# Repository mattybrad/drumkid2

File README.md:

# Drumkid 2
Aleatoric drum machine, uses random numbers to generate/alter drumbeats. This project is the successor to the original Drumkid, which was released in 2020. Drumkid 2 runs on a Raspberry Pi Pico. This repo contains both code for the Pico and PCB files.

## Setup
I used the official Raspberry Pi Pico installer for Windows to set up the Pico toolchain for Visual Studio Code. Remember to update the repo's submodules. The SD card code submodule is a specific commit (v1.1.2), not the latest version. Have included the .vscode folder, which may be different on non-Windows systems?

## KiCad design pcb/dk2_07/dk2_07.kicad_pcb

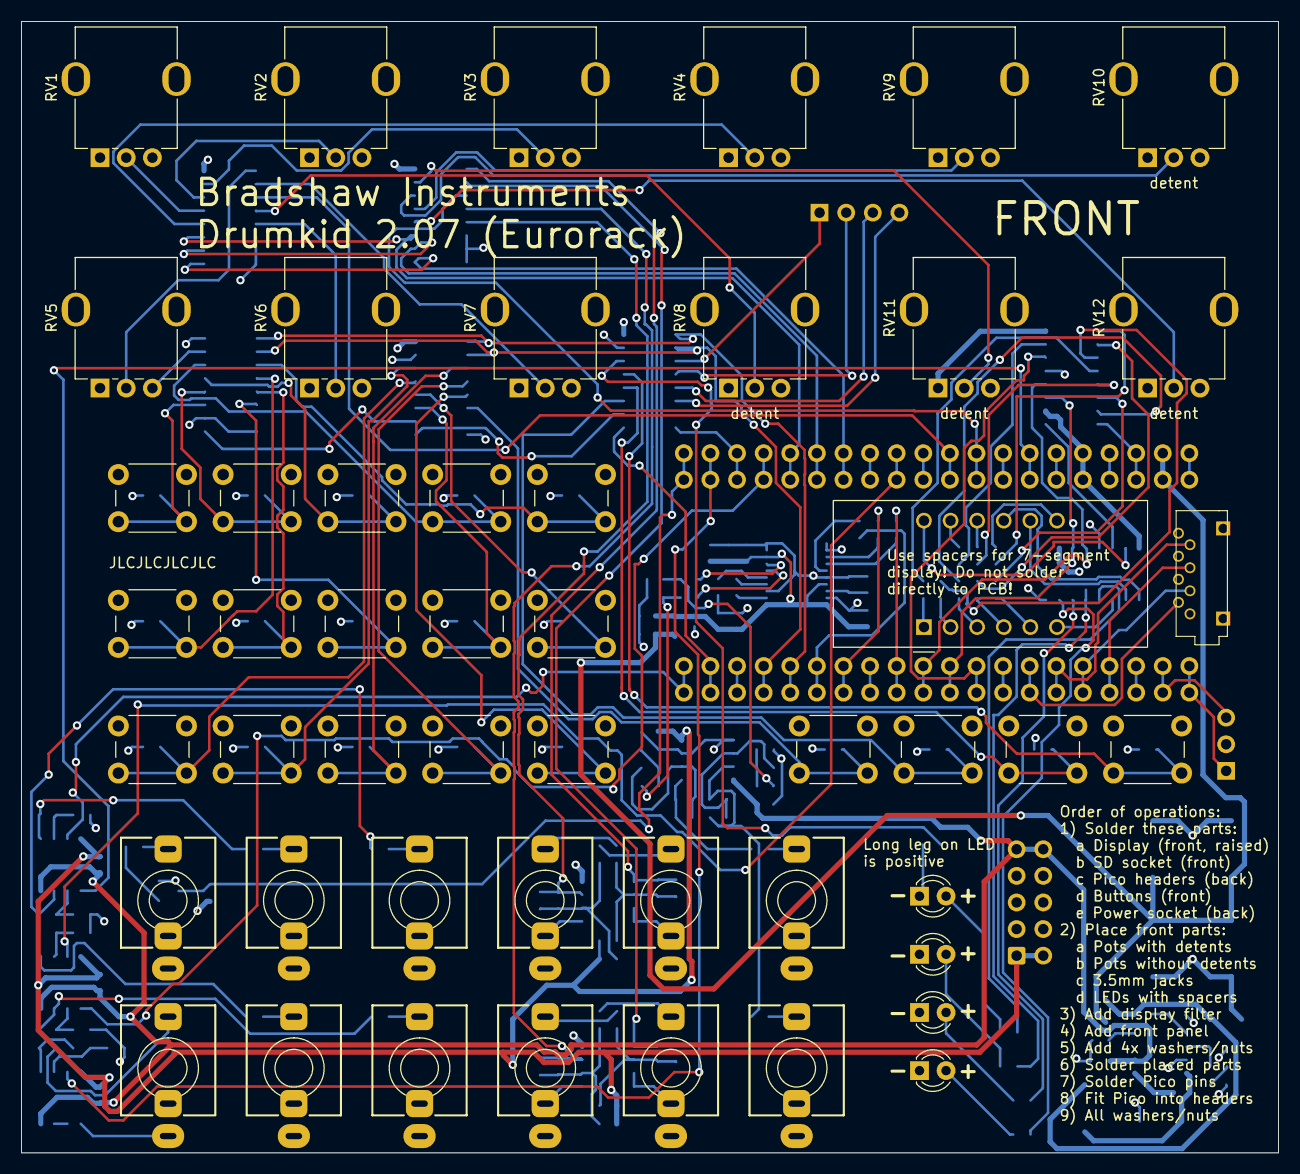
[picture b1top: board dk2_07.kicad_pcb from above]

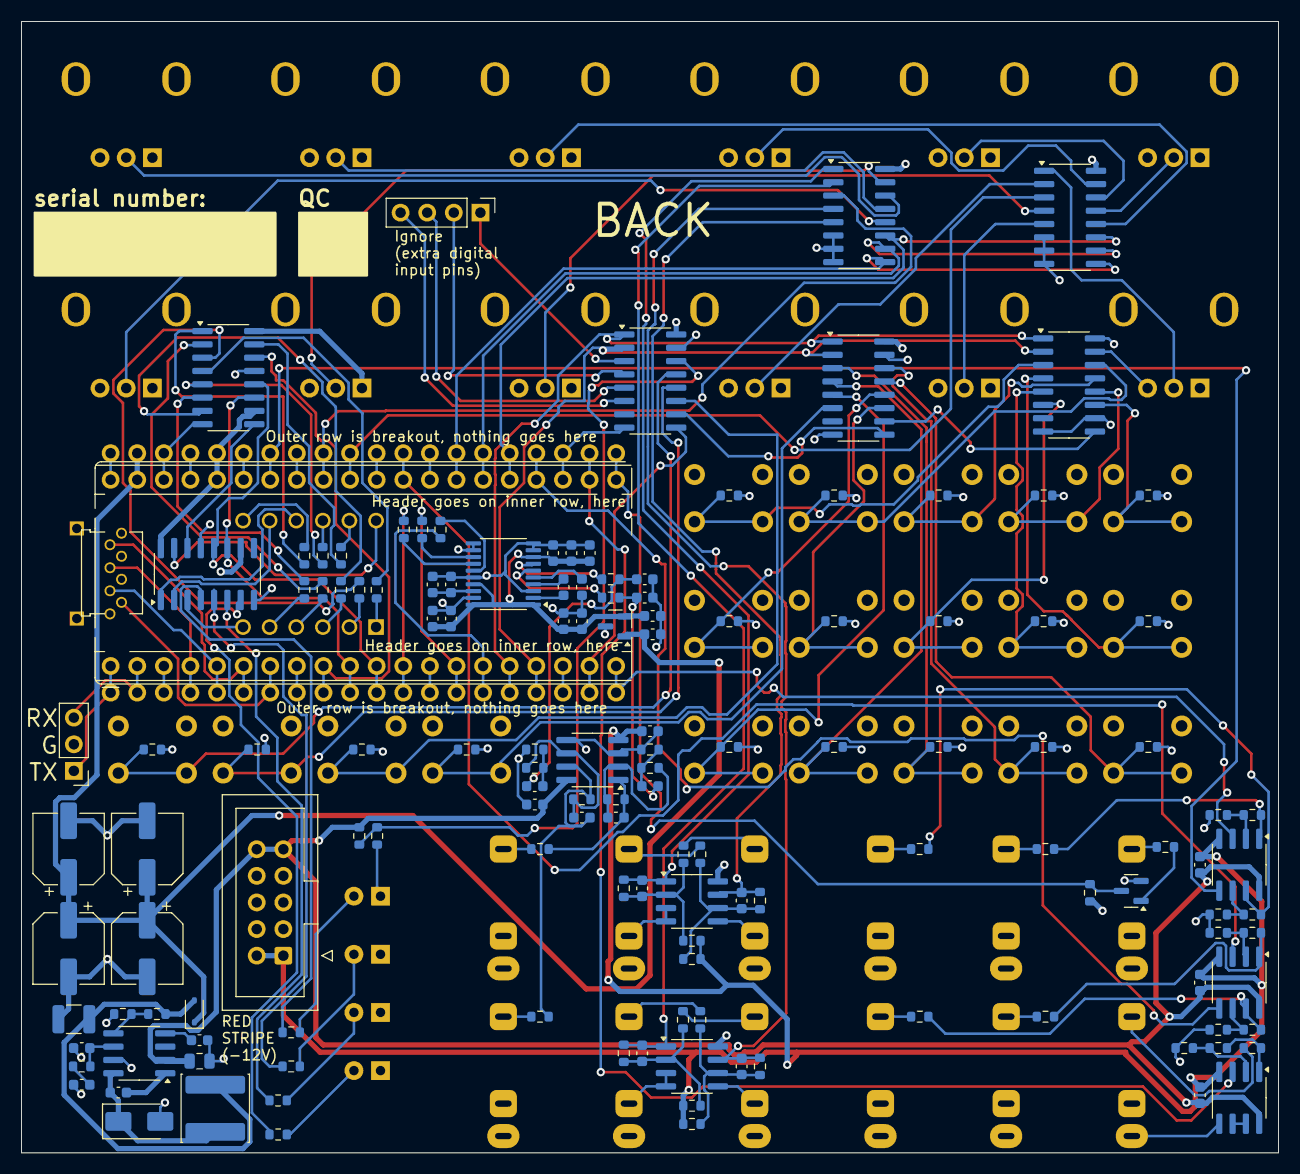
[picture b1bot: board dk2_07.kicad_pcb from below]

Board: 4 copper layers, 120.0 x 108.0 mm, 189 parts (140 on the bottom side), 155 nets.

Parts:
A1: RaspberryPi_Pico; RaspberryPi_Pico_Common_THT_dk2
C1, C2, C3, C4: 1n; C_0603_1608Metric
C5, C9, C24, C29: 1uF; C_0603_1608Metric
C6: 22uF; C_0805_2012Metric
C7: 100nF; C_0603_1608Metric
C8: 8.2nF; C_0603_1608Metric
C10: 1nF; C_0603_1608Metric
C11: 10pF; C_0603_1608Metric
C12: 47uF; C_1210_3225Metric
C13, C14, C15, C16: 470uF; CP_Elec_6.3x7.7
C17, C18, C25, C30, C34: 10uF; C_0603_1608Metric
C19, C20, C36, C37, C38: 100n; C_0603_1608Metric
C21, C22: 18p; C_0603_1608Metric
C23, C28, C31, C32: 0.1uF; C_0603_1608Metric
C26, C27: 2.2uF; C_0603_1608Metric
C33, C35: 2.2nF; C_0603_1608Metric
D1, D2, D3, D4: LED; LED_D3.0mm
D5: B340A; D_SMA
D6: 1N5819WS; D_SOD-323
J1: Trigger_Out_1; Jack_3.5mm_QingPu_WQP-PJ398SM_Vertical
J2: Trigger_Out_2; Jack_3.5mm_QingPu_WQP-PJ398SM_Vertical
J3: Sync_In; Jack_3.5mm_QingPu_WQP-PJ398SM_Vertical
J4: Euro_Out_1; Jack_3.5mm_QingPu_WQP-PJ398SM_Vertical
J5: Micro_SD_Card; YAMAICHI_MICROSD_VERTICAL
J6: Trigger_Out_3; Jack_3.5mm_QingPu_WQP-PJ398SM_Vertical
J7: Trigger_Out_4; Jack_3.5mm_QingPu_WQP-PJ398SM_Vertical
J8: Sync_Out; Jack_3.5mm_QingPu_WQP-PJ398SM_Vertical
J9: Euro_Out_2; Jack_3.5mm_QingPu_WQP-PJ398SM_Vertical
J10: Conn_01x03_Pin; PinHeader_1x03_P2.54mm_Vertical
J11: CV_In_1; Jack_3.5mm_QingPu_WQP-PJ398SM_Vertical
J12: CV_In_2; Jack_3.5mm_QingPu_WQP-PJ398SM_Vertical
J13: CV_In_3; Jack_3.5mm_QingPu_WQP-PJ398SM_Vertical
J14: CV_In_4; Jack_3.5mm_QingPu_WQP-PJ398SM_Vertical
J15: Conn_01x04_Pin; PinHeader_1x04_P2.54mm_Vertical
J16: Eurorack_Power; IDC-Header_2x05_P2.54mm_Vertical
L1: 10uH; L_Sunlord_SWPA6045S
Q1: MMBT3904; SOT-23
R1, R2, R3, R4, R5, R6, R7, R8, R9, R10, R11, R12: 75R; R_0603_1608Metric
R13, R14, R15, R16, R17, R18, R19, R20, R21, R22, R23, R24, R25, R26, R27, R28, R43, R44, R45, R47: 10k; R_0603_1608Metric
R29, R31, R35, R37: 240k; R_0603_1608Metric
R30, R32, R36, R38, R42, R64, R65, R66, R67, R70, R71, R72, R73, R76, R77: 100k; R_0603_1608Metric
R33, R34, R39, R40: 33k; R_0603_1608Metric
R41: 330k; R_0603_1608Metric
R46: 43.2k; R_0603_1608Metric
R48: 1.65k; R_0603_1608Metric
R49, R50, R53, R54: 39k; R_0603_1608Metric
R51, R52: 5.6k; R_0603_1608Metric
R55, R56, R68, R69, R74, R75, R78: 1k; R_0603_1608Metric
R57, R58, R59: 56R; R_0603_1608Metric
R60, R61: 470R; R_0603_1608Metric
R62: 100K; R_0603_1608Metric
R63: 10K; R_0603_1608Metric
RV1, RV2, RV3, RV4, RV5, RV6, RV7, RV8, RV9, RV10, RV11, RV12: 10k; Potentiometer_Alps_RK09K_vertical_biggerholes
SW1, SW2, SW3, SW4, SW5, SW6, SW7, SW8, SW9, SW10, SW11, SW12, SW13, SW14, SW15, SW16, SW17, SW18, SW19: SW_Push; SW_PUSH_6mm
U1, U2: 74HC595; SOIC-16_3.9x9.9mm_P1.27mm
U3: CA56-12EWA; SR410361N
U4, U5, U10: 74HC165; SOIC-16_3.9x9.9mm_P1.27mm
U6, U9: 74HC4051; SOIC-16_3.9x9.9mm_P1.27mm
U7, U8: MCP6002-xSN; SOIC-8_3.9x4.9mm_P1.27mm
U11: AP7333-33SAG; SOT-23
U12: TPS54331DR; SOIC-8_3.9x4.9mm_P1.27mm
U13, U15, U16, U17: TL072; SOIC-8_3.9x4.9mm_P1.27mm
U14: PCM5102; TSSOP-20_4.4x6.5mm_P0.65mm

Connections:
12V DETECTION: R41.1, R42.2, U10.14 (D3)
165_CLOCK: A1.17 (GPIO13), U4.2 (CP), U5.2 (CP), U10.2 (CP)
165_DATA: A1.19 (GPIO14), U10.9 (Q7)
165_LOAD: A1.16 (GPIO12), U4.1 (~PL), U5.1 (~PL), U10.1 (~PL)
595_CLOCK: A1.10 (GPIO7), U1.11 (SRCLK), U2.11 (SRCLK)
595_DATA: A1.9 (GPIO6), U1.14 (SER)
595_LATCH: A1.11 (GPIO8), U1.12 (RCLK), U2.12 (RCLK)
4051_ADDRESS_A: A1.25 (GPIO19), U6.11 (S0), U9.11 (S0)
4051_ADDRESS_B: A1.26 (GPIO20), U6.10 (S1), U9.10 (S1)
4051_ADDRESS_C: A1.27 (GPIO21), U6.9 (S2), U9.9 (S2)
4051_READING_0: A1.31 (GPIO26_ADC0), U6.3 (A)
4051_READING_1: A1.32 (GPIO27_ADC1), U9.3 (A)
+3.3V: A1.36 (3V3), J5.4 (VDD), R63.1, RV1.1, RV2.1, RV3.1, RV4.1, RV5.1, RV6.1, RV7.1, RV8.1, RV9.1, RV10.1, RV11.1, RV12.1, SW1.1, SW2.1, SW3.1, SW4.1, SW5.1, SW6.1, SW7.1, SW8.1, SW9.1, SW10.1, SW11.1, SW12.1, SW13.1, SW14.1, SW15.1, SW16.1, SW17.1, SW18.1, SW19.1, U1.10 (~SRCLR), U1.16 (VCC), U2.10 (~SRCLR), U2.16 (VCC), U4.16 (VCC), U5.16 (VCC), U6.16 (VCC), U7.8 (V+), U8.8 (V+), U9.16 (VCC), U10.16 (VCC)
+3.3VDAC: C9.1, C23.1, C24.1, C25.1, C28.1, C30.1, C32.1, C34.1, U11.2 (VO), U14.1 (CPVDD), U14.8 (AVDD), U14.17 (XSMT), U14.20 (DVDD)
+5V: A1.39 (VSYS), C5.1, C13.1, C14.1, C15.1, C16.1, D6.1 (K), U11.1 (VI)
+12V: C6.1, C19.1, C36.1, C37.1, C38.1, J16.9, J16.10, R41.2, U12.2 (VIN), U13.8 (V+), U15.8 (V+), U16.8 (V+), U17.8 (V+)
-12V: C20.2, C36.2, C37.2, C38.2, J16.1, J16.2, R29.1, R31.1, R35.1, R37.1, U13.4 (V-), U15.4 (V-), U16.4 (V-), U17.4 (V-)
/Shift register in 1/DATA_OUT: U4.9 (Q7), U5.10 (DS)
/Shift register in 2/DATA_OUT: U5.9 (Q7), U10.10 (DS)
CV_IN_1: C1.2, R33.2, U7.1, U9.1 (A4)
CV_IN_2: C2.2, R34.2, U7.7, U9.5 (A5)
CV_IN_3: C3.2, R39.2, U8.1, U9.2 (A6)
CV_IN_4: C4.2, R40.2, U8.7, U9.4 (A7)
DAC_BCLK: A1.14 (GPIO10), R57.1
DAC_DOUT: A1.12 (GPIO9), R58.1
DAC_LRC: A1.15 (GPIO11), R59.1
EURO_OUT_1: J4.T, R55.2
EURO_OUT_2: J9.T, R56.2
GND: A1.3 (GND), A1.8 (GND), A1.13 (GND), A1.18 (GND), A1.23 (GND), A1.28 (GND), A1.33 (AGND), A1.38 (GND), C5.2, C6.2, C8.2, C9.2, C10.2, C11.2, C12.2, C13.2, C14.2, C15.2, C16.2, C19.2, C20.1, C23.2, C24.2, C25.2, C27.2, C28.2, C29.2, C30.2, C31.2, C32.2, C33.2, C34.2, C35.2, D1.1 (K), D2.1 (K), D3.1 (K), D4.1 (K), D5.2 (A), J1.S, J2.S, J3.S, J4.S, J5.6 (VSS), J5.9 (SHIELD), J6.S, J7.S, J8.S, J9.S, J10.2, J11.S, J11.TN, J12.S, J12.TN, J13.S, J13.TN, J14.S, J14.TN, J16.3, J16.4, J16.5, J16.6, J16.7, J16.8, Q1.2 (E), R13.2, R14.2, R15.2, R16.2, R17.2, R18.2, R19.2, R20.2, R21.2, R22.2, R23.2, R24.2, R25.2, R26.2, R27.2, R28.2, R42.1, R43.2, R44.2, R45.2, R48.2, R49.2, R50.2, R64.2, R65.2, R70.2, R71.2, R76.2, RV1.3, RV2.3, RV3.3, RV4.3, RV5.3, RV6.3, RV7.3, RV8.3, RV9.3, RV10.3, RV11.3, RV12.3, U1.8 (GND), U1.13 (~OE), U2.8 (GND), U2.13 (~OE), U4.8 (GND), U4.10 (DS), U4.15 (~CE), U5.8 (GND), U5.15 (~CE), U6.6 (~E), U6.7 (VEE), U6.8 (GND), U7.3 (+), U7.4 (V-), U7.5 (+), U8.3 (+), U8.4 (V-), U8.5 (+), U9.6 (~E), U9.7 (VEE), U9.8 (GND), U10.8 (GND), U10.15 (~CE), U11.3 (GND), U12.7 (GND), U13.3 (+), U13.5 (+), U14.3 (CPGND), U14.9 (AGND), U14.10 (DEMP), U14.11 (FLT), U14.12 (SCK), U14.16 (FMT), U14.19 (DGND), U17.5 (+)
LINE_OUT_L: C17.1, C33.1, R60.2
LINE_OUT_R: C18.1, C35.1, R61.2
unnamed: C10.1, R46.2
unnamed: C17.2, R49.1, R51.1
unnamed: C18.2, R50.1, R52.1
unnamed: C21.2, R53.2, R55.1, U13.1
unnamed: C22.2, R54.2, R56.1, U13.7
unnamed: D1.2 (A), R1.1
unnamed: D2.2 (A), R2.1
unnamed: D3.2 (A), R3.1
unnamed: D4.2 (A), R4.1
unnamed: C7.1, D5.1 (K), L1.1, U12.8 (PH)
unnamed: C12.1, D6.2 (A), L1.2, R47.1
unnamed: J11.T, R30.1
unnamed: J12.T, R32.1
unnamed: J13.T, R36.1
unnamed: J14.T, R38.1
unnamed: J15.1, U10.3 (D4)
unnamed: J15.2, U10.4 (D5)
unnamed: J15.3, U10.5 (D6)
unnamed: J15.4, U10.6 (D7)
unnamed: Q1.1 (B), R62.2
unnamed: R66.1, R68.1, U15.7
unnamed: R67.1, R69.1, U15.1
unnamed: R72.1, R74.1, U16.7
unnamed: R73.1, R75.1, U16.1
unnamed: R77.1, R78.1, U17.1
unnamed: R8.2, U1.15 (QA)
unnamed: R9.2, U1.1 (QB)
unnamed: R10.2, U1.2 (QC)
unnamed: R11.2, U1.3 (QD)
unnamed: R5.2, U1.4 (QE)
unnamed: R12.2, U1.5 (QF)
unnamed: R6.2, U1.6 (QG)
unnamed: U1.9 (QH'), U2.14 (SER)
unnamed: R7.2, U1.7 (QH)
unnamed: U2.15 (QA), U3.12 (CA1)
unnamed: U2.1 (QB), U3.9 (CA2)
unnamed: U2.2 (QC), U3.8 (CA3)
unnamed: U2.3 (QD), U3.6 (CA4)
unnamed: R1.2, U2.4 (QE)
unnamed: R2.2, U2.5 (QF)
unnamed: R3.2, U2.6 (QG)
unnamed: R4.2, U2.7 (QH)
unnamed: R7.1, U3.3 (DPX)
unnamed: R8.1, U3.11 (a)
unnamed: R9.1, U3.7 (b)
unnamed: R10.1, U3.4 (c)
unnamed: R11.1, U3.2 (d)
unnamed: R5.1, U3.1 (e)
unnamed: R12.1, U3.10 (f)
unnamed: R6.1, U3.5 (g)
unnamed: R13.1, SW1.2, U4.11 (D0)
unnamed: R14.1, SW2.2, U4.12 (D1)
unnamed: R15.1, SW3.2, U4.13 (D2)
unnamed: R16.1, SW4.2, U4.14 (D3)
unnamed: R17.1, SW5.2, U4.3 (D4)
unnamed: R18.1, SW6.2, U4.4 (D5)
unnamed: R19.1, SW7.2, U4.5 (D6)
unnamed: R20.1, SW8.2, U4.6 (D7)
unnamed: R21.1, SW9.2, U5.11 (D0)
unnamed: R22.1, SW10.2, U5.12 (D1)
unnamed: R23.1, SW11.2, U5.13 (D2)
unnamed: R24.1, SW12.2, U5.14 (D3)
unnamed: R25.1, SW13.2, U5.3 (D4)
unnamed: R26.1, SW14.2, U5.4 (D5)
unnamed: R27.1, SW15.2, U5.5 (D6)
unnamed: R28.1, SW16.2, U5.6 (D7)
unnamed: RV1.2, U6.13 (A0)
unnamed: RV2.2, U6.14 (A1)
unnamed: RV3.2, U6.15 (A2)
unnamed: RV4.2, U6.12 (A3)
unnamed: RV5.2, U6.1 (A4)
unnamed: RV6.2, U6.5 (A5)
unnamed: RV7.2, U6.2 (A6)
unnamed: RV8.2, U6.4 (A7)
unnamed: C1.1, R29.2, R30.2, R33.1, U7.2 (-)
unnamed: C2.1, R31.2, R32.2, R34.1, U7.6 (-)
unnamed: C3.1, R35.2, R36.2, R39.1, U8.2 (-)
unnamed: C4.1, R37.2, R38.2, R40.1, U8.6 (-)
unnamed: RV9.2, U9.13 (A0)
unnamed: RV10.2, U9.14 (A1)
unnamed: RV11.2, U9.15 (A2)
unnamed: RV12.2, U9.12 (A3)
unnamed: R43.1, SW17.2, U10.11 (D0)
unnamed: R44.1, SW18.2, U10.12 (D1)
unnamed: R45.1, SW19.2, U10.13 (D2)
unnamed: C7.2, U12.1 (BOOT)
unnamed: C11.1, R46.1, U12.6 (COMP)
unnamed: C8.1, U12.4 (SS)
unnamed: R47.2, R48.1, U12.5 (VSENSE)
unnamed: C21.1, R51.2, R53.1, U13.2 (-)
unnamed: C22.1, R52.2, R54.1, U13.6 (-)
unnamed: R57.2, U14.13 (BCK)
unnamed: C26.2, U14.4 (CAPM)
unnamed: C26.1, U14.2 (CAPP)
unnamed: R58.2, U14.14 (DIN)
unnamed: C29.1, C31.1, U14.18 (LDOO)
unnamed: R59.2, U14.15 (LRCK)
unnamed: R60.1, U14.6 (OUTL)
unnamed: R61.1, U14.7 (OUTR)
unnamed: C27.1, U14.5 (VNEG)
unnamed: R65.1, R67.2, U15.2 (-)
unnamed: R64.1, R66.2, U15.6 (-)
unnamed: R71.1, R73.2, U16.2 (-)
unnamed: R70.1, R72.2, U16.6 (-)
unnamed: R76.1, R77.2, U17.2 (-)
unnamed: U17.6 (-), U17.7
SD_CHIP_SELECT: A1.7 (GPIO5), J5.2 (DAT3/CD)
SD_CLOCK: A1.4 (GPIO2), J5.5 (CLK)
SD_SERIAL_IN: A1.5 (GPIO3), J5.3 (CMD)
SD_SERIAL_OUT: A1.6 (GPIO4), J5.7 (DAT0)
SERIAL_RX: A1.2 (GPIO1), J10.3
SERIAL_TX: A1.1 (GPIO0), J10.1
SYNC_IN: A1.21 (GPIO16), Q1.3 (C), R63.2
SYNC_IN_EURO: J3.T, R62.1
SYNC_OUT: A1.22 (GPIO17), U17.3 (+)
SYNC_OUT_EURO: J8.T, R78.2
TRIGGER_OUT_1: A1.20 (GPIO15), U15.3 (+)
TRIGGER_OUT_1_EURO: J1.T, R69.2
TRIGGER_OUT_2: A1.34 (GPIO28_ADC2), U15.5 (+)
TRIGGER_OUT_2_EURO: J2.T, R68.2
TRIGGER_OUT_3: A1.29 (GPIO22), U16.3 (+)
TRIGGER_OUT_3_EURO: J6.T, R75.2
TRIGGER_OUT_4: A1.24 (GPIO18), U16.5 (+)
TRIGGER_OUT_4_EURO: J7.T, R74.2

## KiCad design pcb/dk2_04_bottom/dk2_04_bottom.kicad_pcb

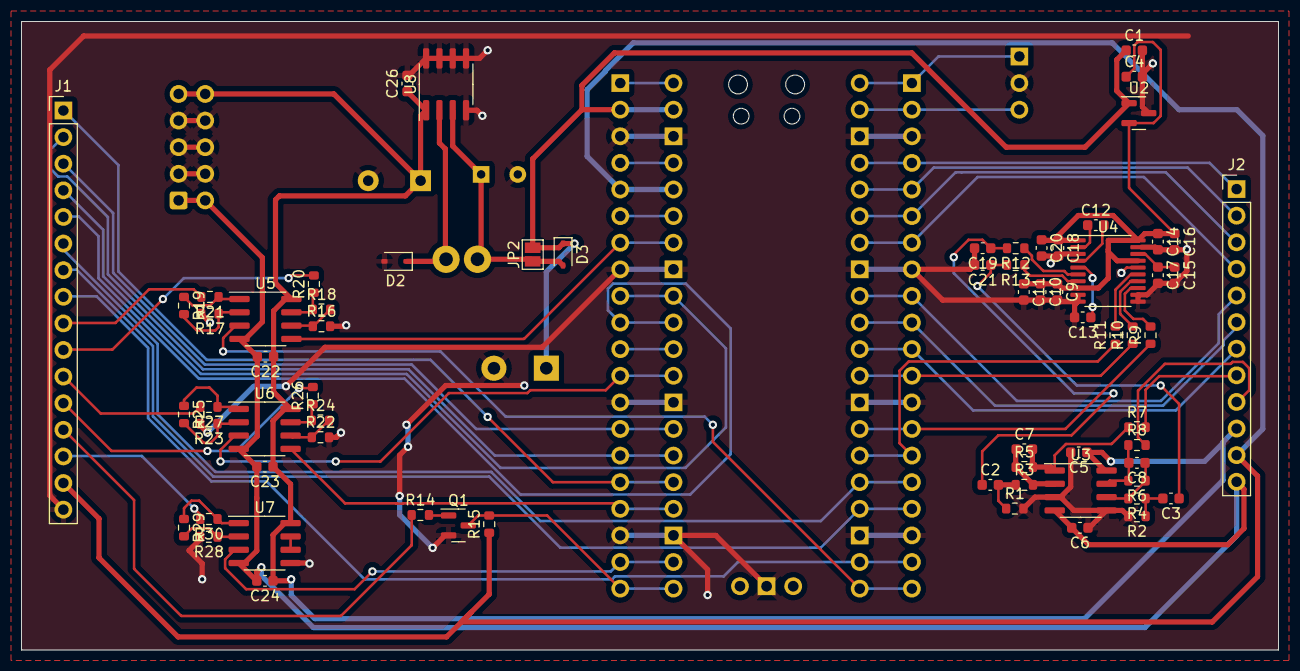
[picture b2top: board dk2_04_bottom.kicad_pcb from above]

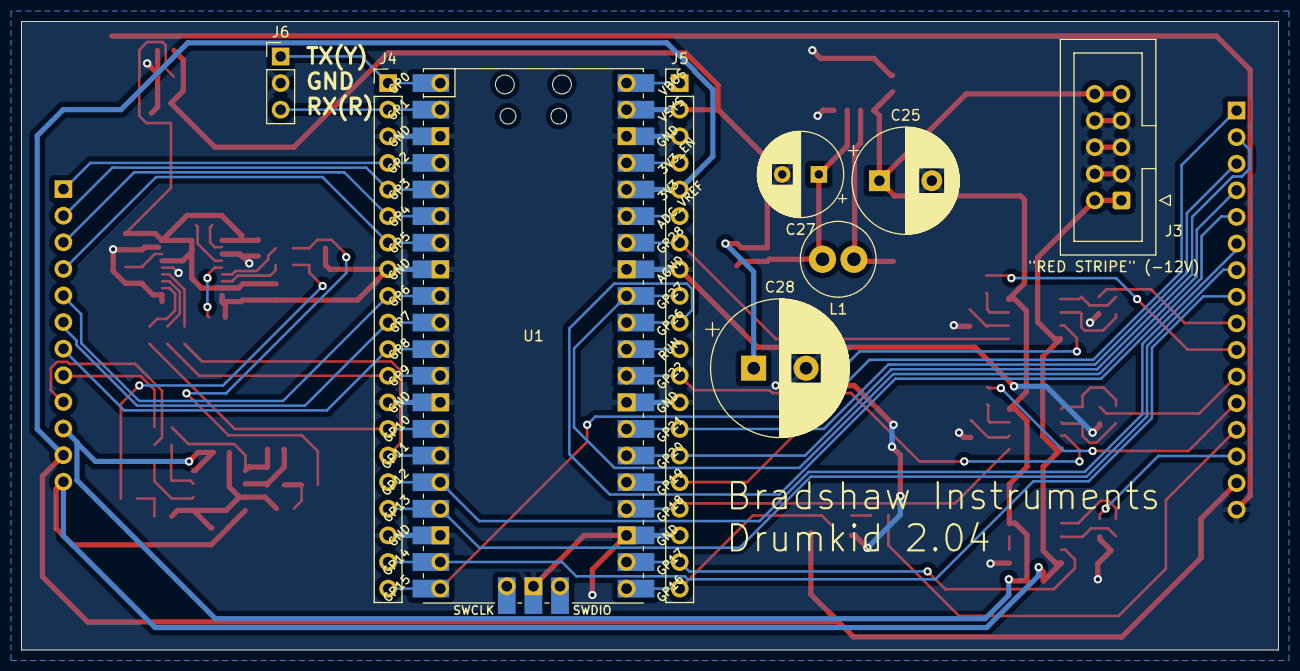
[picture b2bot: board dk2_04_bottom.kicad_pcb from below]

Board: 2 copper layers, 120.0 x 60.0 mm, 77 parts (9 on the bottom side), 71 nets.

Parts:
C1, C4, C10, C15, C26: 1uF; C_0603_1608Metric
C2, C3, C11, C16, C20: 10uF; C_0603_1608Metric
C5, C6, C22, C23, C24: 100n; C_0603_1608Metric
C7, C8: 18p; C_0603_1608Metric
C9, C14, C17, C18: 0.1uF; C_0603_1608Metric
C12, C13: 2.2uF; C_0603_1608Metric
C19, C21: 2.2nF; C_0603_1608Metric
C25: 470uF 35V; CP_Radial_D10.0mm_P5.00mm
C27: 180uF 35V; CP_Radial_D8.0mm_P3.50mm
C28: 2200uF; CP_Radial_D13.0mm_P5.00mm
D2, D3: 1N5819WS; D_SOD-323
J1: Left_Header; PinHeader_1x16_P2.54mm_Vertical
J2: Right_Header; PinHeader_1x12_P2.54mm_Vertical
J3: Eurorack_Power; IDC-Header_2x05_P2.54mm_Vertical
J4, J5: Conn_01x20_Pin; PinHeader_1x20_P2.54mm_Vertical
J6: Conn_01x03_Pin; PinHeader_1x03_P2.54mm_Vertical
JP2: SolderJumper_2_Open; SolderJumper-2_P1.3mm_Open_Pad1.0x1.5mm
L1: 68uH/2A; L_Radial_D7.0mm_P3.00mm
Q1: MMBT3904; SOT-23
R1, R2, R5, R6: 39k; R_0603_1608Metric
R3, R4: 5.6k; R_0603_1608Metric
R7, R8, R20, R21, R26, R27, R30: 1k; R_0603_1608Metric
R9, R10, R11: 56R; R_0603_1608Metric
R12, R13: 470R; R_0603_1608Metric
R14: 100K; R_0603_1608Metric
R15: 10K; R_0603_1608Metric
R16, R17, R18, R19, R22, R23, R24, R25, R28, R29: 100k; R_0603_1608Metric
U1: Pico; RPi_Pico_SMD_TH
U2: AP7333-33SAG; SOT-23
U3, U5, U6, U7: TL072; SOIC-8_3.9x4.9mm_P1.27mm
U4: PCM5102; TSSOP-20_4.4x6.5mm_P0.65mm
U8: XL1509-5.0; SOIC-8_3.9x4.9mm_P1.27mm

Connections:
165_CLOCK: J1.7, J4.17, U1.17 (GPIO13)
165_DATA: J1.8, J4.19, U1.19 (GPIO14)
165_LOAD: J1.6, J4.16, U1.16 (GPIO12)
595_CLOCK: J2.6, J4.10, U1.10 (GPIO7)
595_DATA: J2.5, J4.9, U1.9 (GPIO6)
595_LATCH: J2.7, J4.11, U1.11 (GPIO8)
4051_ADDRESS_A: J1.1, J5.16, U1.25 (GPIO19)
4051_ADDRESS_B: J1.2, J5.15, U1.26 (GPIO20)
4051_ADDRESS_C: J1.3, J5.14, U1.27 (GPIO21)
4051_READING_0: J1.5, J5.10, U1.31 (GPIO26_ADC0)
4051_READING_1: J1.4, J5.9, U1.32 (GPIO27_ADC1)
+3.3V: J1.15, J2.11, J5.5, R15.1, U1.36 (3V3)
+3.3VDAC: C4.1, C9.1, C10.1, C11.1, C14.1, C16.1, C18.1, C20.1, U2.2 (VO), U4.1 (CPVDD), U4.8 (AVDD), U4.17 (XSMT), U4.20 (DVDD)
+5V: C1.1, C28.1, D3.1 (K), J5.2, JP2.2 (B), U1.39 (VSYS), U2.1 (VI)
+12V: C5.1, C22.1, C23.1, C24.1, C25.1, C26.1, J2.10, J3.9, J3.10, U3.8 (V+), U5.8 (V+), U6.8 (V+), U7.8 (V+), U8.1 (VIN)
-12V: C6.2, C22.2, C23.2, C24.2, J2.12, J3.1, J3.2, U3.4 (V-), U5.4 (V-), U6.4 (V-), U7.4 (V-)
DAC_BCLK: J4.14, R9.1, U1.14 (GPIO10)
DAC_DOUT: J4.12, R10.1, U1.12 (GPIO9)
DAC_LRC: J4.15, R11.1, U1.15 (GPIO11)
EURO_OUT_1: J2.8, R7.2
EURO_OUT_2: J2.9, R8.2
GND: C1.2, C4.2, C5.2, C6.1, C9.2, C10.2, C11.2, C13.2, C14.2, C15.2, C16.2, C17.2, C18.2, C19.2, C20.2, C21.2, C25.2, C26.2, C27.2, C28.2, D2.2 (A), J1.16, J3.3, J3.4, J3.5, J3.6, J3.7, J3.8, J4.3, J4.8, J4.13, J4.18, J5.3, J5.8, J5.13, J5.18, J6.2, Q1.2 (E), R1.2, R2.2, R16.2, R17.2, R22.2, R23.2, R28.2, U1.3 (GND), U1.8 (GND), U1.13 (GND), U1.18 (GND), U1.23 (GND), U1.28 (GND), U1.33 (AGND), U1.38 (GND), U1.42 (GND), U2.3 (GND), U3.3 (+), U3.5 (+), U4.3 (CPGND), U4.9 (AGND), U4.10 (DEMP), U4.11 (FLT), U4.12 (SCK), U4.16 (FMT), U4.19 (DGND), U7.5 (+), U8.4 (~EN), U8.5 (GND), U8.6 (GND), U8.7 (GND), U8.8 (GND)
LINE_OUT_L: C2.1, C19.1, R12.2
LINE_OUT_R: C3.1, C21.1, R13.2
unnamed: C2.2, R1.1, R3.1
unnamed: C3.2, R2.1, R4.1
unnamed: C7.2, R5.2, R7.1, U3.1
unnamed: C8.2, R6.2, R8.1, U3.7
unnamed: D2.1 (K), L1.1, U8.2 (OUT)
unnamed: C27.1, D3.2 (A), JP2.1 (A), L1.2, U8.3 (FB)
unnamed: Q1.1 (B), R14.2
unnamed: R18.1, R20.1, U5.7
unnamed: R19.1, R21.1, U5.1
unnamed: R24.1, R26.1, U6.7
unnamed: R25.1, R27.1, U6.1
unnamed: R29.1, R30.1, U7.1
unnamed: C7.1, R3.2, R5.1, U3.2 (-)
unnamed: C8.1, R4.2, R6.1, U3.6 (-)
unnamed: R9.2, U4.13 (BCK)
unnamed: C12.2, U4.4 (CAPM)
unnamed: C12.1, U4.2 (CAPP)
unnamed: R10.2, U4.14 (DIN)
unnamed: C15.1, C17.1, U4.18 (LDOO)
unnamed: R11.2, U4.15 (LRCK)
unnamed: R12.1, U4.6 (OUTL)
unnamed: R13.1, U4.7 (OUTR)
unnamed: C13.1, U4.5 (VNEG)
unnamed: R17.1, R19.2, U5.2 (-)
unnamed: R16.1, R18.2, U5.6 (-)
unnamed: R23.1, R25.2, U6.2 (-)
unnamed: R22.1, R24.2, U6.6 (-)
unnamed: R28.1, R29.2, U7.2 (-)
unnamed: U7.6 (-), U7.7
SD_CHIP_SELECT: J2.4, J4.7, U1.7 (GPIO5)
SD_CLOCK: J2.1, J4.4, U1.4 (GPIO2)
SD_SERIAL_IN: J2.2, J4.5, U1.5 (GPIO3)
SD_SERIAL_OUT: J2.3, J4.6, U1.6 (GPIO4)
SERIAL_RX: J4.2, J6.3, U1.2 (GPIO1)
SERIAL_TX: J4.1, J6.1, U1.1 (GPIO0)
SYNC_IN: J5.20, Q1.3 (C), R15.2, U1.21 (GPIO16)
SYNC_IN_EURO: J1.13, R14.1
SYNC_OUT: J5.19, U1.22 (GPIO17), U7.3 (+)
SYNC_OUT_EURO: J1.14, R30.2
TRIGGER_OUT_1: J4.20, U1.20 (GPIO15), U5.3 (+)
TRIGGER_OUT_1_EURO: J1.9, R21.2
TRIGGER_OUT_2: J5.7, U1.34 (GPIO28_ADC2), U5.5 (+)
TRIGGER_OUT_2_EURO: J1.10, R20.2
TRIGGER_OUT_3: J5.12, U1.29 (GPIO22), U6.3 (+)
TRIGGER_OUT_3_EURO: J1.11, R27.2
TRIGGER_OUT_4: J5.17, U1.24 (GPIO18), U6.5 (+)
TRIGGER_OUT_4_EURO: J1.12, R26.2

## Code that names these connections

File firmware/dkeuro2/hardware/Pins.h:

#pragma once

namespace Pins {
    
    // SD card pins
    constexpr uint8_t SD_CLOCK = 2;
    constexpr uint8_t SD_SERIAL_IN = 3;
    constexpr uint8_t SD_SERIAL_OUT = 4;
    constexpr uint8_t SD_CHIP_SELECT = 5;

    // shift register pins (74HC595 for output, 74HC165 for input)
    constexpr uint8_t SR_OUT_DATA = 6;
    constexpr uint8_t SR_OUT_CLOCK = 7;
    constexpr uint8_t SR_OUT_LATCH = 8;
    constexpr uint8_t SR_IN_DATA = 14;
    constexpr uint8_t SR_IN_CLOCK = 13;
    constexpr uint8_t SR_IN_LOAD = 12;

    // multiplexer (4051) pins
    constexpr uint8_t MUX_ADDRESS_A = 19;
    constexpr uint8_t MUX_ADDRESS_B = 20;
    constexpr uint8_t MUX_ADDRESS_C = 21;
    constexpr uint8_t MUX_READ_0 = 26;
    constexpr uint8_t MUX_READ_1 = 27;
    constexpr uint8_t ADC_SMPS_MODE = 23;

    // DAC (audio output) pins
    constexpr uint8_t DAC_DOUT = 9;
    constexpr uint8_t DAC_BCLK = 10;
    constexpr uint8_t DAC_LRC = 11;

    // clock/sync pins
    constexpr uint8_t SYNC_IN = 16;
    constexpr uint8_t SYNC_OUT = 17;

    // trigger output pins
    constexpr uint8_t TRIGGER_1 = 15;
    constexpr uint8_t TRIGGER_2 = 28;
    constexpr uint8_t TRIGGER_3 = 22;
    constexpr uint8_t TRIGGER_4 = 24;
}

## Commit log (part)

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2023-06-12 playing on laptop
2023-06-16 started actual dk source code
2023-06-16 some weird timing error with LEDs but promising nonetheless
2023-06-19 making led and button functions a bit nicer
2023-06-20 solved temperamental 4051 readings
2023-06-20 debouncing kinda works
2023-06-22 readme update
2023-06-22 sync out works
2023-07-17 start/stop and tempo
2023-08-09 front panel taking shape
2023-08-15 started eurorack pcb
2023-08-15 going for a picnic
2023-08-16 pcb layout going well
2023-08-16 there is a lot of stuff on this pcb
2023-08-16 more layout tweaks
2023-08-21 changing design to double-decker pcb for compactness
2023-08-23 bottom pcb looks fairly easy
2023-08-23 done for the week, started routing
2023-08-29 routing again
2023-08-29 top routing done
2023-08-29 started component placement on bottom board
2023-08-30 bottom pcb placement done
2023-08-30 routing done
2023-08-30 ready for jlcpcb
2023-09-05 panel nearly done
2023-10-11 assembling the pcb 2.02
2023-10-18 pcb looking good so far
2023-11-06 notes
2023-11-08 sd card working in cpp
2023-11-08 sd sample loading works (messy for now)
2023-11-10 code getting better gtg
2023-11-10 input/output handling now done with timers, much cleaner
2023-11-14 improved debouncing
2023-11-14 i broke everything
2023-11-14 pointers are annoying, part 1 of many, but it works again
2023-11-14 updated notes
2023-11-18 fixed flash problem
2023-11-20 a big mess
2023-11-21 restored samples
2023-11-21 stereo!!
2023-11-25 debugging working
2023-11-28 mainly fixed SD conflict
2023-11-28 parsing wav files from sd nicely
2023-11-28 sample loading from WAV file works really nicely!
2023-11-28 lost in flash
2023-11-29 more adventures in flash
2023-12-04 reading non-44-byte wav headers successfully
2023-12-04 moving some code to better places
2023-12-04 now loading entire sample set from SD to flash to RAM
2023-12-05 program now checks the flash on boot, also upgraded to 1MB flash
2023-12-05 tempo now stored when beat stops, also some bugfixes
2023-12-05 sync in working
2023-12-12 notes about swing
2023-12-12 unsuccessful attempt at multicore stuff
2023-12-12 new scheduler working for now
2023-12-12 first attempt at swing
2024-01-08 re-added start/stop
2024-01-09 scheduler now references beat
2024-01-09 chance working nicely combined with cv
2024-01-09 implemented range and midpoint
2024-01-09 midpoint cv working
2024-01-15 time signature support
2024-01-16 trying to find an annoying bug, making a mess
2024-01-16 kinda deleted everything and regretted it
2024-01-16 it's all bad today
2024-01-19 reduced clicks by adding small fade-out before retrigger
2024-01-19 missing hit
2024-01-22 fixed issue with initial hits on start
2024-01-22 sync out timing fixed
2024-01-22 zoom cv
2024-01-23 replaced janky timer system with proper alarm pool stuff
2024-01-23 made some improvements to very high speed performance
2024-01-23 messy but good beat/tuplet stuff
2024-01-29 adding alphabet characters
2024-01-30 displaying alphabet characters works well now, sd card stuff is hard
2024-01-30 can handle longer samples
2024-02-06 messing with tuplets again
2024-02-09 finding/fixing(?) some high-speed bugs
2024-02-09 added long press functionality
2024-02-12 switched sample position/speed stuff from floats to ints
2024-02-12 lerping! much better pitch effect
2024-02-13 tidied up lerp stuff, added drop function
2024-02-13 moving from floats to ints for timing
2024-02-16 have hit a slight wall
2024-02-23 much more efficient
2024-02-23 new scheduling system working so far
2024-02-26 code speed now really good, hitting 1000BPM+ with ints
2024-02-27 restored trigger/sync outs
2024-02-27 started trying to figure out reverse sample offset, got tired
2024-03-05 performance monitoring
2024-03-05 added dead zones to pots
2024-03-05 started pitch dead zone
2024-03-11 tuplet bug fixed
2024-03-12 improved display stuff
2024-03-12 beats can be saved to flash
2024-03-15 sync in messy but nice!
2024-03-15 ppqn stuff
2024-03-19 internal and external clock coexisting peacefully
2024-03-19 swing restored
2024-03-19 negative velocity
2024-03-20 tuplets work with sync in
2024-03-22 swing now available in 8ths or 16ths
2024-03-22 display pulse
2024-03-26 handling menu edge cases
2024-03-26 cluster
2024-04-02 added second drop control for random hits
2024-04-08 figuring out performance stuff
2024-04-10 ppqn output setting, clear current beat
2024-05-17 better chance implementation, first attempt at magnet
2024-05-22 so close to magnet function working but not quite right with discontinuity right now
2024-05-24 magnet works okay
2024-05-31 live beat edit
2024-05-31 revert beat to previous saved version
2024-05-31 new bottom pcb
2024-06-04 bootup visuals, error handling, status LEDs
2024-06-04 improved save behaviour
2024-06-04 crop control works
2024-06-04 crop in reverse
2024-06-04 crush volume compensation
2024-06-24 settings menu working nicely
2024-06-25 settings saved with wear levelling
2024-06-25 bug fixes
2024-06-26 settings save process working v nicely
2024-06-26 output options moved to settings menu
2024-07-01 pcb progress
2024-07-02 bottom pcb shrunk
2024-07-02 a commit before i mess up all the buttons
2024-07-05 top pcb routed
2024-07-05 routing bottom pcb
2024-07-08 bottom pcb routed
2024-07-08 fixed an issue where i forgot to rotate the pots on the pcb
2024-07-08 panel very nearly done
2024-07-09 pcbs ordered
2024-07-23 re-added clock mode setting
2024-07-23 fixed sync out tuplet issue
2024-07-29 tweaks and faffing
2024-08-05 making repo more portable
2024-08-05 submodule issues
2024-08-19 it all got too messy
2024-08-19 bare minimum code working
2024-08-20 some good timing stability improvements
2024-08-23 tried something, it didn't work
2024-08-23 a commit while everything works
2024-08-23 ppqn is back
2024-09-02 rewriting beat object for new microstep system
2024-09-02 horrible code, trying something
2024-09-05 BACK IN THE GAME
2024-09-06 new dac timing working well with 1ppqn sync in
2024-09-06 nice stable timing with sync in
2024-09-11 temporarily adding PIO blink program for testing
2024-09-11 shift out using PIO
2024-09-11 PIO shift in working pretty well
2024-09-11 analog stuff is back and slightly nicer
2024-09-11 basic reimplementation of chance knob
2024-09-16 display and menu almost working again
2024-09-17 tempo and time signature settings working
2024-09-17 beat groups working
2024-09-23 about to do output pulses but ran out of time
2024-09-27 slightly bodged sync output
2024-09-30 ppqn stuff and glitch effect
2024-09-30 pitch
2024-09-30 checking performance
2024-10-04 button hold
2024-10-07 step edit working well
2024-10-07 backup or revert beat
2024-10-08 basic live edit
2024-10-08 improved performance a lot, live edit pretty good
2024-10-11 timing tweaks
2024-10-14 restored velocity
2024-10-14 vel and vel range knobs
2024-11-05 lower sample rates working
2024-11-05 stereo downmix supported!
2024-11-05 added sample tails to reduce pop/click sounds
2024-11-18 figuring out how to do factory reset
2024-11-18 added old drumkid beats
2024-11-19 pot centre deadzones, fixed pulse display issue
2024-11-19 new event system works well
2024-11-21 swing working fairly well
2024-11-21 swing and zoom playing nicely together
2024-11-22 cluster control working
2024-11-22 magnet control working (that was annoying)
2024-11-22 tweaked live edit
2024-11-22 drop controls working again
2024-11-22 fractional tempos, magnet fix
2024-11-23 settings save works
2024-11-25 started manual
2024-11-25 error system improved
2024-11-25 minor tweaks
2024-11-25 finally got button debouncing working properly
2024-11-26 committing before i start messing about too much with timing stuff
2024-11-28 big progress with external sync
2024-11-28 IMPROVEMENTS
2024-11-29 autosave working much better
2024-12-06 next pcb started
2024-12-06 yet more manual
2024-12-09 manual manual
2024-12-09 improved clear function
2024-12-10 hacking info in manual
2024-12-10 power off stuff
2024-12-12 GETTING THERE!
2024-12-13 sample... samples
2024-12-13 todo
2025-02-17 panel improvements
2025-02-19 rejigged top board, smaller connectors
2025-03-11 autosave works
2025-03-11 more qc success
2025-03-12 more qc and some debug config
2025-03-12 even more qc and some flash stuff
2025-03-19 everything working well but about to start faffing with flash addresses
2025-03-20 massive faff trying to clean up flash system
2025-03-24 will this work? pre-commit script thing...
2025-03-24 sorry for all the commits
2025-05-15 haven't committed for ages because i did something stupid in git
2025-05-15 layout starting to feel okay, routing will be bad..?
2025-05-16 panel and pcb are aligned
2025-05-16 started routing
2025-05-19 more routing
2025-05-19 ROUTING
2025-05-19 27 unrouted, nearly there...
2025-05-20 faffing with capacitors for jlc reasons
2025-08-04 pcb and panel v2.06, minor fixes
2025-09-10 some experiments
2025-09-24 minor timing tweaks
2025-09-24 created image of front panel
2025-10-24 can now use longer folder names and more folders
2025-10-24 firmware todo list
2025-12-01 pcb v2.07 nearly done
2025-12-09 serial number silkscreen, assembly order adjusted
2026-01-09 firmware v2 started
2026-01-12 pll stuff working fairly well
2026-01-13 clock not working properly, making some changes...
2026-01-13 pll thing working pretty well
2026-01-13 shift register output working with PIO
2026-01-14 led functions working well
2026-01-14 an undignified mixture of v1 timing fixes and v2 led progress
2026-01-15 buttons started
2026-01-16 fixed issue where metronome didn't play in ext clock mode
2026-01-19 fixed issue where tempos above 999.9BPM didn't display correctly
2026-01-19 fixed issue where tempo was wrong when switching from external clock to internal
2026-01-21 reimplemented pulseGpio (as pulseTrigger) and pulseLed
2026-01-22 removed redundant code
2026-01-23 looking at ways to do longer samples for v2 firmware
2026-01-26 wrestling with update loop
2026-01-28 4 channels working but code got a bit messy
2026-01-28 sort of progress, weird ringing sound
2026-01-28 a bit tidier...
2026-01-29 really happy with audio loop now, nice clean code
2026-01-29 decent transport triggering implementation
2026-01-29 tried out ~20s of sample storage, works well
2026-01-30 moved hardware update code from timers to main loop for predictability
2026-01-30 fixed timing error with main loop hardware updates
2026-02-01 slight file tidy
2026-02-04 reading files from SD card
2026-02-05 making some progress with flash memory stuff
2026-02-05 sd stuff messy but working
2026-02-05 it's late
2026-02-06 loading works well, leaving for now
2026-02-06 made a mess, testing buttons, kit loading, etc
2026-02-25 some progress with wav parser but 24 bit samples broken
2026-02-27 24-bit! 32-bit! weird 7-byte header chunks!
2026-03-01 basic stereo to mono summing
2026-03-01 create config file for max channels etc
2026-03-03 better button handling, 7-segment improvements
2026-03-06 thinking about multi kit mode
2026-03-25 midway through big update to add multiple kits
2026-03-25 messily gradually moving towards multi kit loading
2026-03-27 aaah much nicer menu logic
2026-03-27 we have audio again! very close to multi-kit
2026-04-06 I CAN CHANGE KITS INSTANTLY
2026-04-06 function exists to figure out whether to move kits but can't actually move them yet
2026-04-13 fixed invalid metadata, kit loading works nicely!
2026-04-14 menu/loading/display improvements
2026-04-16 beat class works
2026-04-16 analog(ue) inputs working
2026-04-16 basic aleatory working
2026-04-17 velocity implemented
2026-04-17 taking a little break
2026-04-24 switching timing system from fixed PPQN to Q16.16
2026-05-29 i've got a todo list, things are taking shape...
2026-06-01 about to try some radical changes to transport
2026-06-01 transport update reasonable so far
2026-06-02 manual tempo broadly working
2026-06-09 haven't committed for a bit
2026-06-15 some external clock progress maybe
2026-06-18 can now switch between clock modes
2026-06-18 display/menu/transport improvements
